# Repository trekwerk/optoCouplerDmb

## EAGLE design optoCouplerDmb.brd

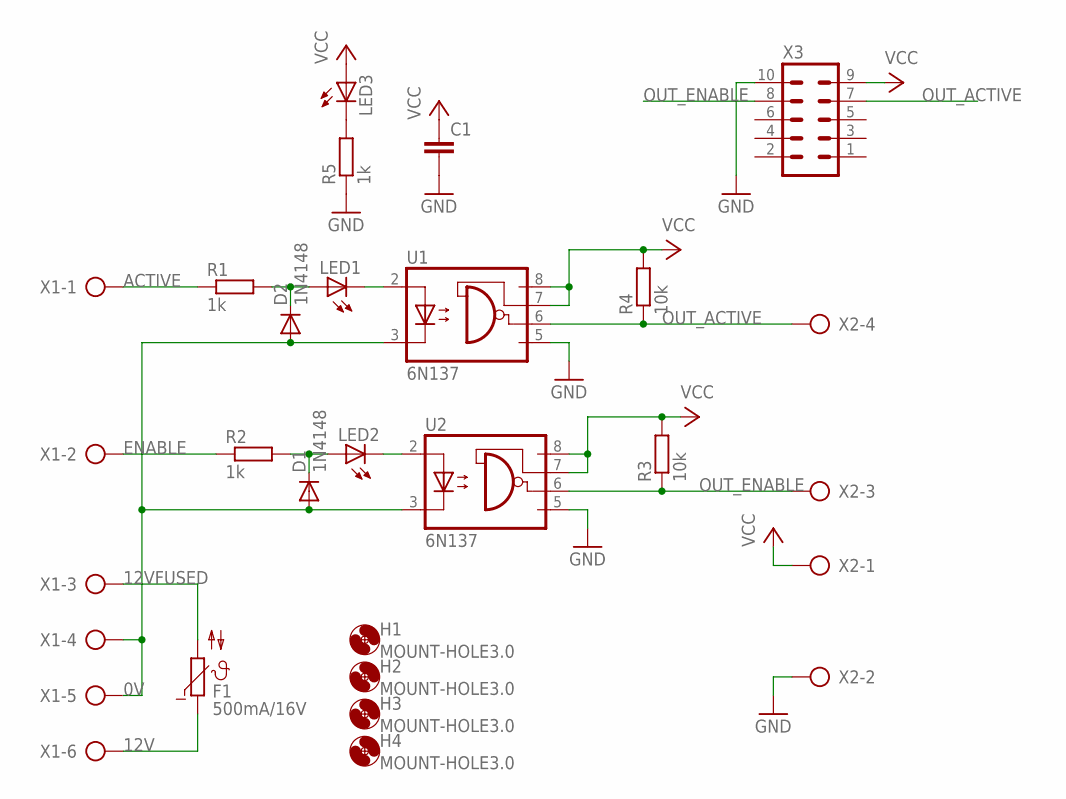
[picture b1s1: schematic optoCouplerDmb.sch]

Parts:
C1: C-EU050-030X075; C050-030X075
D1, D2: 1N4148; DO35-7
F1: 500mA/16V; B57164
H1, H2, H3, H4: MOUNT-HOLE3.0; 3,0
LED1, LED2, LED3: LED3MM
R1, R2, R5: 1k; 0207/10
R3, R4: 10k; 0207/10
U1, U2: 6N137; DIL08
X1: AK500/6
X2: AK500/4
X3: ML10

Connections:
0V: D1.A, D2.A, U1.3 (C), U2.3 (C), X1.4, X1.5
12V: F1.1, X1.6
12VFUSED: F1.2, X1.3
ACTIVE: R1.1, X1.1
ENABLE: R2.1, X1.2
GND: C1.2, R5.1, U1.5 (GND), U2.5 (GND), X2.2, X3.10
unnamed: D2.C, LED1.A, R1.2
unnamed: LED1.K (C), U1.2 (A)
unnamed: LED3.K (C), R5.2
unnamed: LED2.K (C), U2.2 (A)
unnamed: D1.C, LED2.A, R2.2
OUT_ACTIVE: R4.1, U1.6 (VO), X2.4, X3.7
OUT_ENABLE: R3.1, U2.6 (VO), X2.3, X3.8
VCC: C1.1, LED3.A, R3.2, R4.2, U1.7 (VE), U1.8 (VCC), U2.7 (VE), U2.8 (VCC), X2.1, X3.9

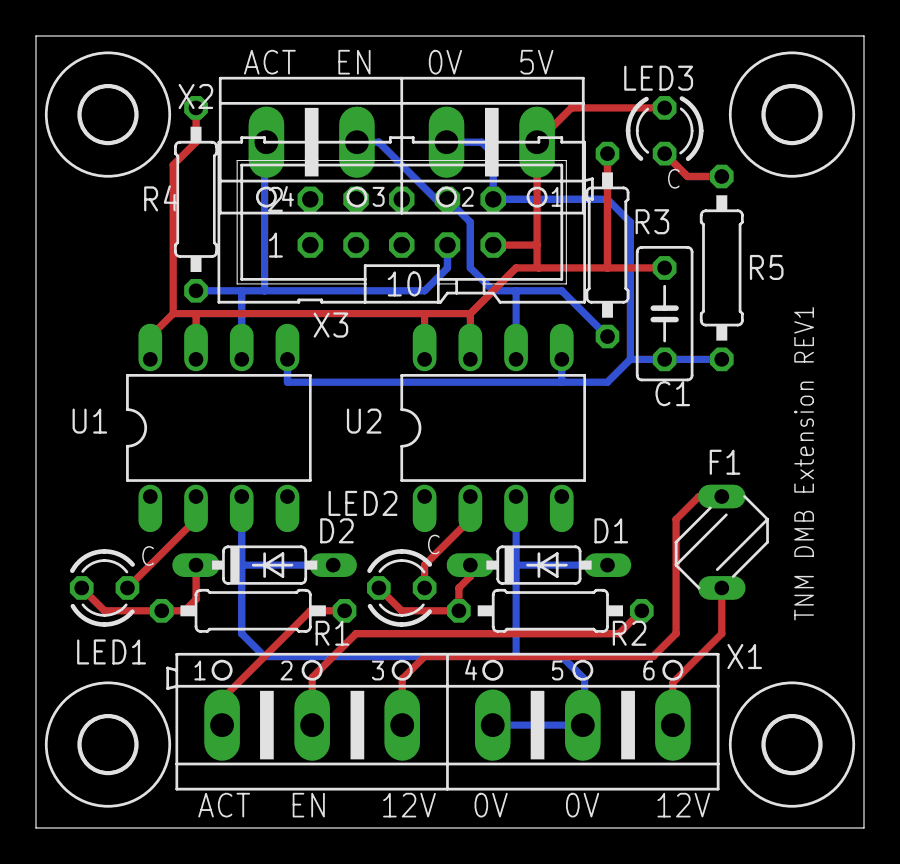
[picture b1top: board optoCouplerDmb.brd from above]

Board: 2 copper layers, 46.0 x 44.0 mm, 21 parts (0 on the bottom side), 14 nets.

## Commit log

2013-09-16 eagle files
2013-09-16 resistors 10mm , added led
